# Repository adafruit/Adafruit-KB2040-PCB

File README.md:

## Adafruit KB2040 - RP2040 Kee Boar Driver PCB

<a href="http://www.adafruit.com/products/5302"><br/>
Click here to purchase one from the Adafruit shop</a>

PCB files for the Adafruit KB2040 - RP2040 Kee Boar Driver. 

Format is EagleCAD schematic and board layout
* https://www.adafruit.com/product/5302

### Description

A wild Kee Boar appears! It’s a shiny KB2040! An Arduino Pro Micro-shaped board for Keebs with RP2040. (#keeblife 4 evah) A lot of folks like using Adafruit parts for their Keeb builds – but with the ItsyBitsy not being pin-compatible with the Pro Micro pinout, it really wasn't very easy without some sort of adapter plate.

Now we’re seeing lots of people use CircuitPython for keebs, which is awesome! So why not try our hands at spinning up a pro-micro-compatible RP2040 board? The RP2040 is plenty powerful, low-cost, and makes for an excellent keeb driver chip.

We mixed together what we liked most about the SparkFun Pro Micro RP2040 (Qwiic / STEMMA QT I2C port on the end, so good!) and Elite-C (castellated pads & pins for D+ and D-) and our existing RP2040 boards (boot button can be used for user, 8MB QSPI flash, onboard NeoPixel, jumper for skipping the diode/fuse for high power RGB LEDs or USB hosting). We even got it to all fit on a 2-layer PCB with 7/7 routing – just needed to make the smallest caps and resistors 0402. 

With 20 GPIO available (18 on castellated pins, 2 on STEMMA QT port) you can easily make up to 100-keys matrices, or common 65% 5x15 layouts. Use a plug-and-play QT cable to connect to the last two pins without having to do any desoldering/rework.

### License

Adafruit invests time and resources providing this open source design, please support Adafruit and open-source hardware by purchasing products from [Adafruit](https://www.adafruit.com)!

Designed by Limor Fried/Ladyada for Adafruit Industries.

Creative Commons Attribution/Share-Alike, all text above must be included in any redistribution. 
See license.txt for additional details.

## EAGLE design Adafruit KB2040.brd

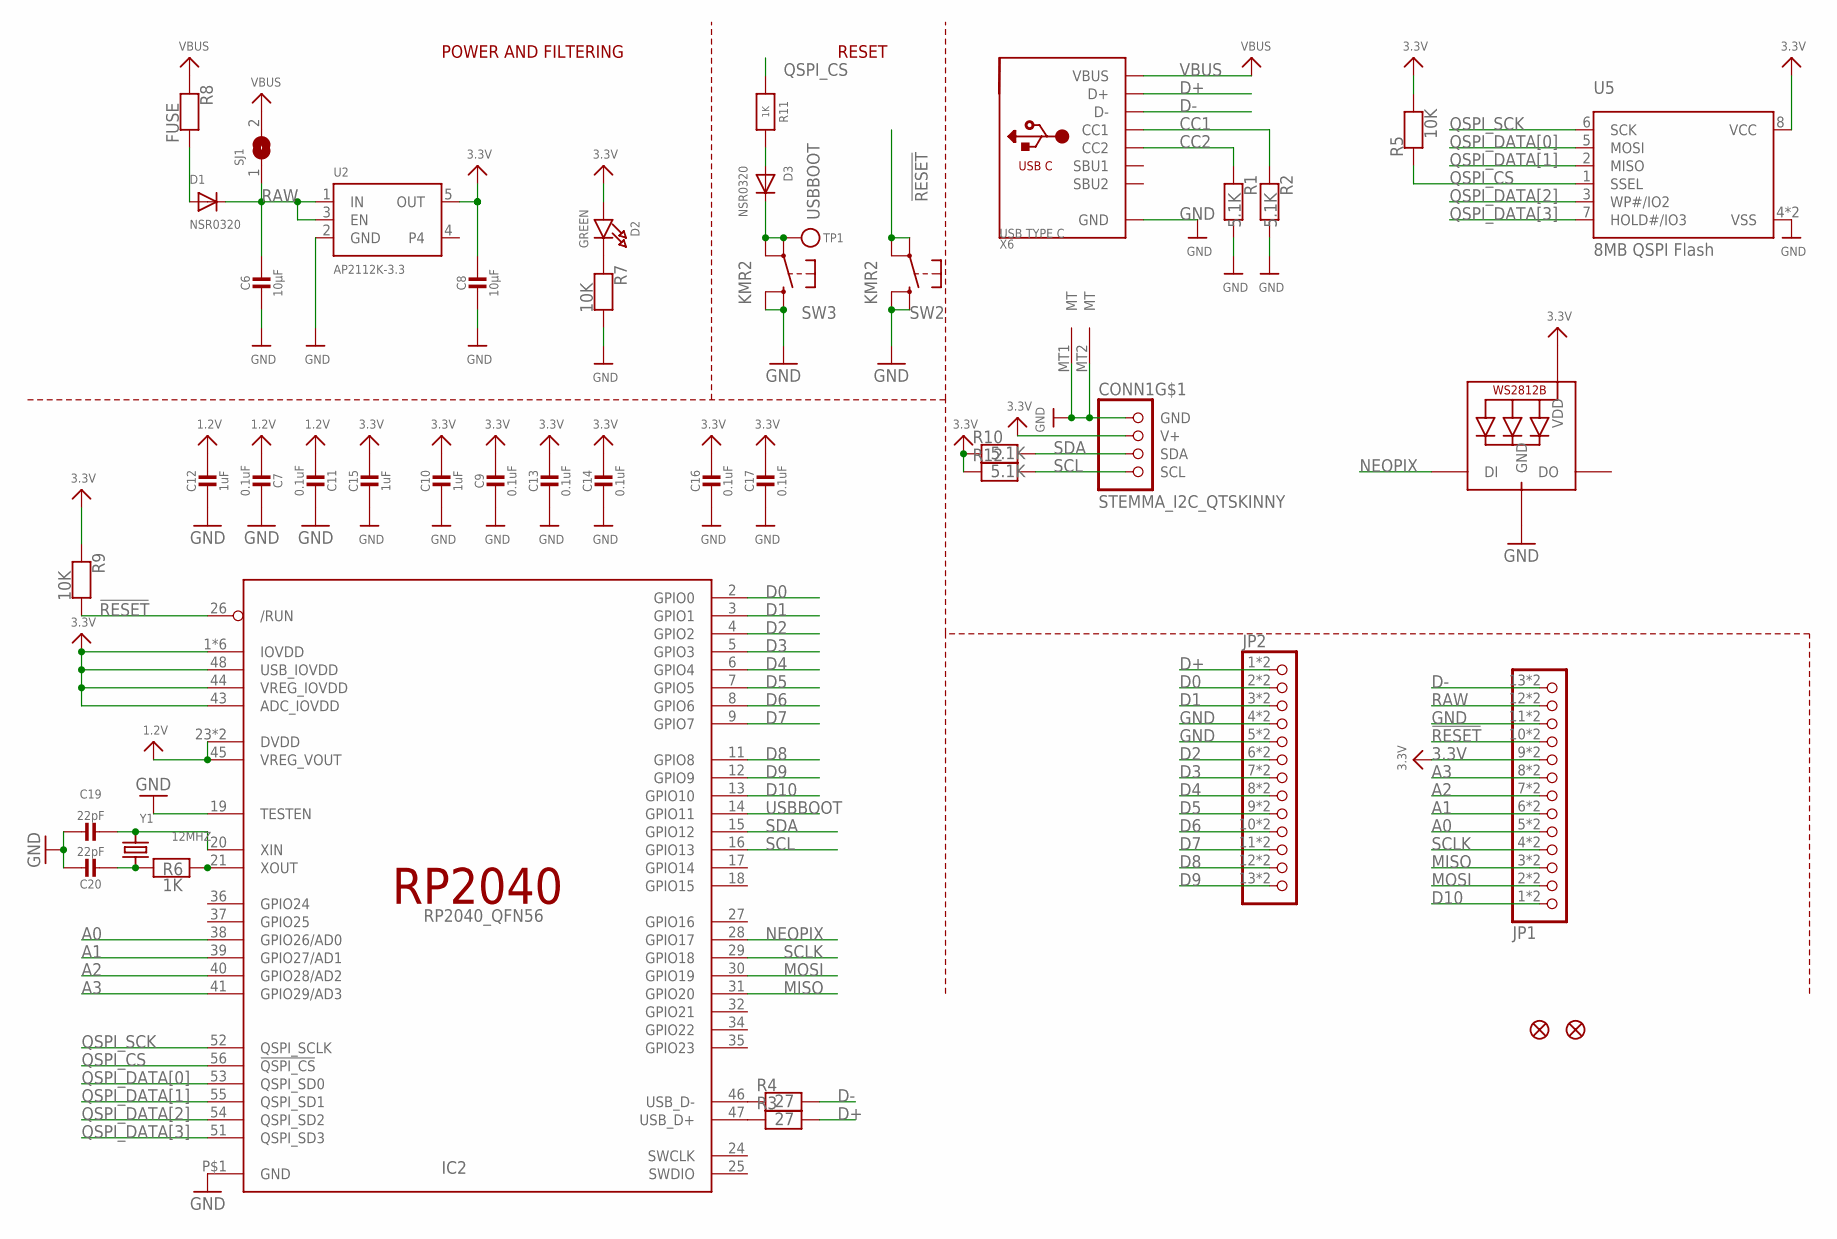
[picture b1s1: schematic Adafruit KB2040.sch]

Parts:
C6, C8: 10µF; _0805MP
C7, C9, C11, C13, C14, C16, C17: 0.1uF; _0402NO
C10, C12: 1uF; _0603MP
C15: 1uF; 0603-NO
C19, C20: 22pF; _0402NO
CONN1: STEMMA_I2C_QTSKINNY; JST_SH4_SKINNY
D1, D3: NSR0320; SOD-323F
D2: GREEN; CHIPLED_0603_NOOUTLINE
IC2: RP2040_QFN56; QFN56_7MM_REDUCEDEPAD
JP1, JP2: HEADER-1X13_CASTEL; 1X13_CASTEL
LED1: WS2812B_SK6805_1515; SK6805_1515
R1, R2, R10, R12: 5.1K; _0402NO
R3, R4: 27; _0402NO
R5, R7, R9: 10K; _0402NO
R6, R11: 1K; _0402NO
R8: FUSE; 0805-NO
SJ1: SOLDERJUMPER; SOLDERJUMPER_ARROW_NOPASTE
SW2, SW3: KMR2; BTN_KMR2_4.6X2.8
TP1: TESTPOINTROUND1.5MMNO; TESTPOINT_ROUND_1.5MM_NO
U2: AP2112K-3.3; SOT23-5
U5: 8MB QSPI Flash; USON8_4X4
U$34, U$35: FIDUCIAL_1MM
X6: USB TYPE C; USB_C_CUSB31-CFM2AX-01-X
Y1: 12MHZ; CRYSTAL_2.5X2

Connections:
1.2V: C7.2, C11.2, C12.1, IC2.23 (DVDD), IC2.45 (VREG_VOUT), IC2.50 (DVDD)
3.3V: C8.1, C9.1, C10.1, C13.1, C14.1, C15.1, C16.1, C17.1, CONN1.2 (V+), D2.A, IC2.1 (IOVDD), IC2.10 (IOVDD), IC2.22 (IOVDD), IC2.33 (IOVDD), IC2.42 (IOVDD), IC2.43 (ADC_IOVDD), IC2.44 (VREG_IOVDD), IC2.48 (USB_IOVDD), IC2.49 (IOVDD), JP1.9, JP1.9C (9), LED1.2 (VDD), R5.2, R9.1, R10.1, R12.1, U2.5 (OUT), U5.8 (VCC)
!RESET: IC2.26 (/RUN), JP1.10, JP1.10C (10), R9.2, SW2.A, SW2.A' (P1)
A0: IC2.38 (GPIO26/AD0), JP1.5, JP1.5C (5)
A1: IC2.39 (GPIO27/AD1), JP1.6, JP1.6C (6)
A2: IC2.40 (GPIO28/AD2), JP1.7, JP1.7C (7)
A3: IC2.41 (GPIO29/AD3), JP1.8, JP1.8C (8)
CC1: R2.1, X6.A5 (CC1)
CC2: R1.1, X6.B5 (CC2)
D0: IC2.2 (GPIO0), JP2.2, JP2.2C (2)
D1: IC2.3 (GPIO1), JP2.3, JP2.3C (3)
D2: IC2.4 (GPIO2), JP2.6, JP2.6C (6)
D3: IC2.5 (GPIO3), JP2.7, JP2.7C (7)
D4: IC2.6 (GPIO4), JP2.8, JP2.8C (8)
D5: IC2.7 (GPIO5), JP2.9, JP2.9C (9)
D6: IC2.8 (GPIO6), JP2.10, JP2.10C (10)
D7: IC2.9 (GPIO7), JP2.11, JP2.11C (11)
D8: IC2.11 (GPIO8), JP2.12, JP2.12C (12)
D9: IC2.12 (GPIO9), JP2.13, JP2.13C (13)
D10: IC2.13 (GPIO10), JP1.1, JP1.1C (1)
D+: JP2.1, JP2.1C (1), R3.2, X6.A6 (D+), X6.B6 (D+)
D-: JP1.13, JP1.13C (13), R4.2, X6.A7 (D-), X6.B7 (D-)
GND: C6.2, C7.1, C8.2, C9.2, C10.2, C11.1, C12.2, C13.2, C14.2, C15.2, C16.2, C17.2, C19.1, C20.1, CONN1.1 (GND), CONN1.MT1 (MT), CONN1.MT2 (MT), IC2.19 (TESTEN), IC2.P$1 (GND), JP1.11, JP1.11C (11), JP2.4, JP2.4C (4), JP2.5, JP2.5C (5), LED1.4 (GND), R1.2, R2.2, R7.2, SW2.B (S), SW2.B' (S1), SW3.B (S), SW3.B' (S1), U2.2 (GND), U5.4 (VSS), U5.PAD (VSS), X6.A1B12 (GND), X6.B1A12 (GND)
MISO: IC2.31 (GPIO20), JP1.3, JP1.3C (3)
MOSI: IC2.30 (GPIO19), JP1.2, JP1.2C (2)
unnamed: IC2.47 (USB_D+), R3.1
unnamed: D2.C, R7.1
unnamed: IC2.46 (USB_D-), R4.1
unnamed: D3.A, R11.2
unnamed: C19.2, IC2.20 (XIN), Y1.3 (2)
unnamed: C20.2, R6.1, Y1.1
unnamed: IC2.21 (XOUT), R6.2
unnamed: D1.A, R8.2
NEOPIX: IC2.28 (GPIO17), LED1.1 (DI)
QSPI_CS: IC2.56 (!QSPI_CS), R5.1, R11.1, U5.1 (SSEL)
QSPI_DATA[0]: IC2.53 (QSPI_SD0), U5.5 (MOSI)
QSPI_DATA[1]: IC2.55 (QSPI_SD1), U5.2 (MISO)
QSPI_DATA[2]: IC2.54 (QSPI_SD2), U5.3 (WP#/IO2)
QSPI_DATA[3]: IC2.51 (QSPI_SD3), U5.7 (HOLD#/IO3)
QSPI_SCK: IC2.52 (QSPI_SCLK), U5.6 (SCK)
RAW: C6.1, D1.C, JP1.12, JP1.12C (12), SJ1.1, U2.1 (IN), U2.3 (EN)
SCL: CONN1.4 (SCL), IC2.16 (GPIO13), R12.2
SCLK: IC2.29 (GPIO18), JP1.4, JP1.4C (4)
SDA: CONN1.3 (SDA), IC2.15 (GPIO12), R10.2
USBBOOT: D3.C, IC2.14 (GPIO11), SW3.A, SW3.A' (P1), TP1.P$1
VBUS: R8.1, SJ1.2, X6.A4B9 (VBUS), X6.B4A9 (VBUS)

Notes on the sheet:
POWER AND FILTERING
RESET

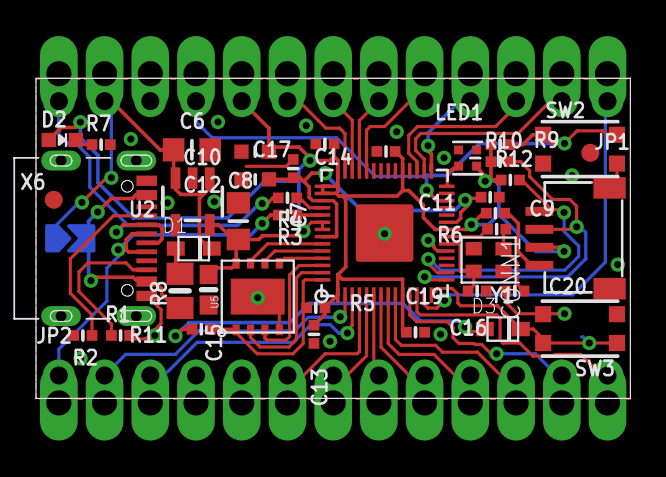
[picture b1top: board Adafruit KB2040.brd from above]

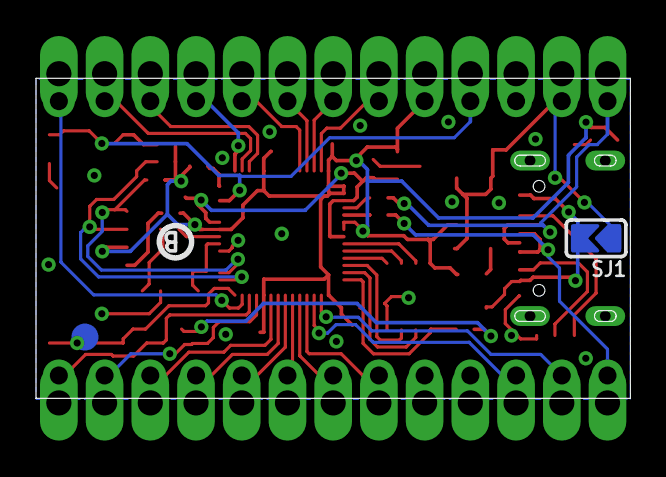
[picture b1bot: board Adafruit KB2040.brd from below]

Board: 2 copper layers, 33.0 x 17.8 mm, 47 parts (4 on the bottom side), 46 nets.

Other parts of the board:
U$17: KB2040_BOT
U$19: KB2040_TOP
U$20: PCBFEAT-REV-040

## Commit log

2021-12-03 Add factory reset file.
2021-12-03 Update name.
2021-12-03 Add PrettyPins PDF

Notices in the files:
parts and their libraries:
microbuilder: This work is placed in the public domain, and may be freely used for commercial and non-commercial work with the following conditions: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
